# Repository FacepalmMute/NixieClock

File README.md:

# NixieClock
Combining Nixie tube technology with IoT
* Providing vintage style Nixie tube clock suitability for daily use.
* Building of a basis for testing and demonstrating IoT stuff using
  the [ESP8266](
  http://www.google.de/search?hl=de&source=hp&biw=&bih=&q=Mikrocontroller.net+ESP8266
  "Mikrocontroller.net ESP8266 - Google-Suche") in conjunction with
  the Arduino library.
* Open documentation allows designing of individual boxes, using of
  miscellaneous Nixie tubes, software and so forth within your own
  handicraft work.
  
# Firmware
The _firmware_ can be found in the Arduino folder. Compilation was
tested under Arduino.cc. You might use the libraries found in the
library folder. At least you will need the _NixieClock_
software. _DS1307RTC, Time-master_, and _Timezone-master_ are
available in their unimproved versions from Arduino and are assumed to
be yet part of your Arduino standard software installation. When using
the Arduino build system you can use any version you like without
problems.

When using Arduino Eclipse plugins you will get into trouble caused by
the redirection of the standard c-header file _Time.h_ that was done
in _Time-master._ This strange hijacking of the original _time.h_ is
responsible for wrecking the build process of the ESP8266 core
_arduino.ar._ So Eclipse users will likely use my modified versions of
_DS1307RTC, Time-master_, and _Timezone-master_ where I removed the
annoying redirection and detaching of standard headers.

Furthermore there are the two Arduino sketch folders _Nixie4_ and
_Nixie6._ _Nixie4_ is the firmware used by our 4 tube prototype;
_Nixie6_ is used by our 6 tube prototype.

## Prototype with 4 ИН-1 Nixie tubes
![Prototype ИН-1 Nixie clock](./pic/P1010273_s.jpg "4x ИН-1 tube
type")

This clock is an implementation with 4 ИН-1 Nixie tubes. 

## Prototype with 6 ИН-12А Nixie tubes
![Prototype ИН-12А Nixie clock](./pic/P1010278_s.jpg "6x ИН-12А tube
type")

# Hardware Description
![Beware of electric shock!](./pic/High_Voltage.jpg "Beware of
electric shock!")

**Beware of electric shock!**

**Beware of electrical safety hazards!**

**The Nixie tubes are fired at approx 200 Volt! There is definitely a
danger of hazardous voltage given! Never think of working on the Nixie
hardware when you are not educated in doing work with hazardous
voltages!**

The hardware description is given in EAGLE format and a PDF-file.

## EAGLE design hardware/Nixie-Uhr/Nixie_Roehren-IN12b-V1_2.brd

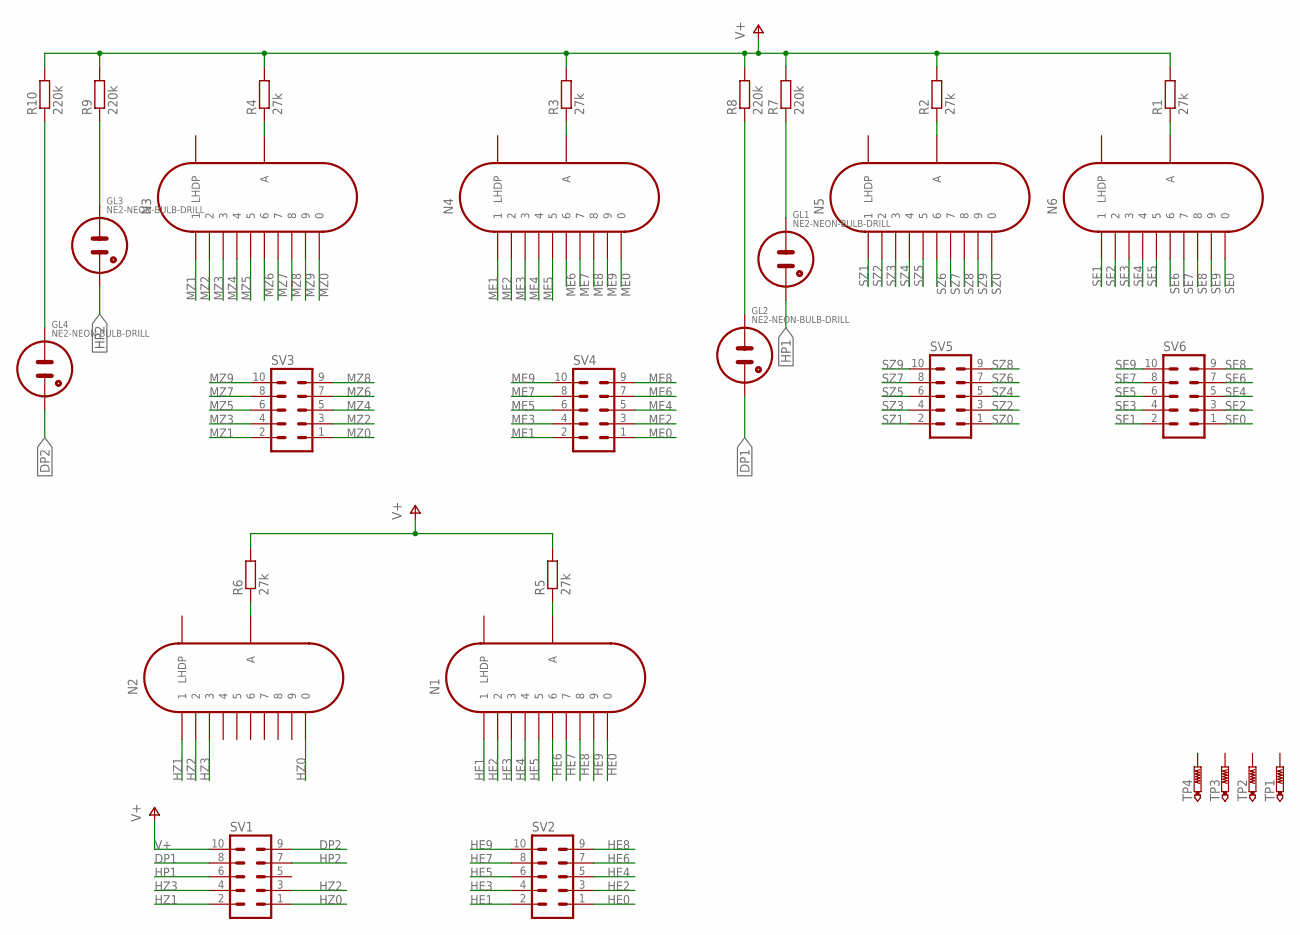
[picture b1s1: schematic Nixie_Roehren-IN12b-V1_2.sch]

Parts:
GL1, GL2, GL3, GL4: NE2-NEON-BULB-DRILL
N1, N2, N3, N4, N5, N6: IN-12B; IN-12
R1, R2, R3, R4, R5, R6: 27k; 0207/10
R7, R8, R9, R10: 220k; 0207/10
SV1, SV2, SV3, SV4, SV5, SV6: ML10
TP1, TP2, TP3, TP4: PTR1B1,27; B1,27

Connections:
DP1: GL2.2 (A1), SV1.8
DP2: GL4.2 (A1), SV1.9
HE0: N1.0, SV2.1
HE1: N1.1, SV2.2
HE2: N1.2, SV2.3
HE3: N1.3, SV2.4
HE4: N1.4, SV2.5
HE5: N1.5, SV2.6
HE6: N1.6, SV2.7
HE7: N1.7, SV2.8
HE8: N1.8, SV2.9
HE9: N1.9, SV2.10
HP1: GL1.2 (A1), SV1.6
HP2: GL3.2 (A1), SV1.7
HZ0: N2.0, SV1.1
HZ1: N2.1, SV1.2
HZ2: N2.2, SV1.3
HZ3: N2.3, SV1.4
ME0: N4.0, SV4.1
ME1: N4.1, SV4.2
ME2: N4.2, SV4.3
ME3: N4.3, SV4.4
ME4: N4.4, SV4.5
ME5: N4.5, SV4.6
ME6: N4.6, SV4.7
ME7: N4.7, SV4.8
ME8: N4.8, SV4.9
ME9: N4.9, SV4.10
MZ0: N3.0, SV3.1
MZ1: N3.1, SV3.2
MZ2: N3.2, SV3.3
MZ3: N3.3, SV3.4
MZ4: N3.4, SV3.5
MZ5: N3.5, SV3.6
MZ6: N3.6, SV3.7
MZ7: N3.7, SV3.8
MZ8: N3.8, SV3.9
MZ9: N3.9, SV3.10
unnamed: N2.A, R6.1
unnamed: N6.A, R1.1
unnamed: N5.A, R2.1
unnamed: N4.A, R3.1
unnamed: N3.A, R4.1
unnamed: GL2.1 (A), R8.1
unnamed: N1.A, R5.1
unnamed: GL1.1 (A), R7.1
unnamed: GL4.1 (A), R10.1
unnamed: GL3.1 (A), R9.1
SE0: N6.0, SV6.1
SE1: N6.1, SV6.2
SE2: N6.2, SV6.3
SE3: N6.3, SV6.4
SE4: N6.4, SV6.5
SE5: N6.5, SV6.6
SE6: N6.6, SV6.7
SE7: N6.7, SV6.8
SE8: N6.8, SV6.9
SE9: N6.9, SV6.10
SZ0: N5.0, SV5.1
SZ1: N5.1, SV5.2
SZ2: N5.2, SV5.3
SZ3: N5.3, SV5.4
SZ4: N5.4, SV5.5
SZ5: N5.5, SV5.6
SZ6: N5.6, SV5.7
SZ7: N5.7, SV5.8
SZ8: N5.8, SV5.9
SZ9: N5.9, SV5.10
V+: R1.2, R2.2, R3.2, R4.2, R5.2, R6.2, R7.2, R8.2, R9.2, R10.2, SV1.10

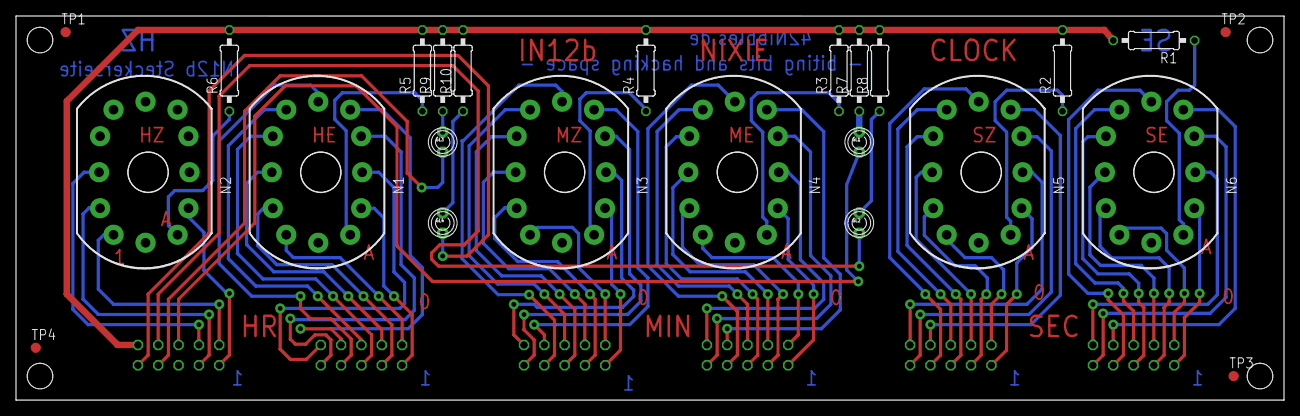
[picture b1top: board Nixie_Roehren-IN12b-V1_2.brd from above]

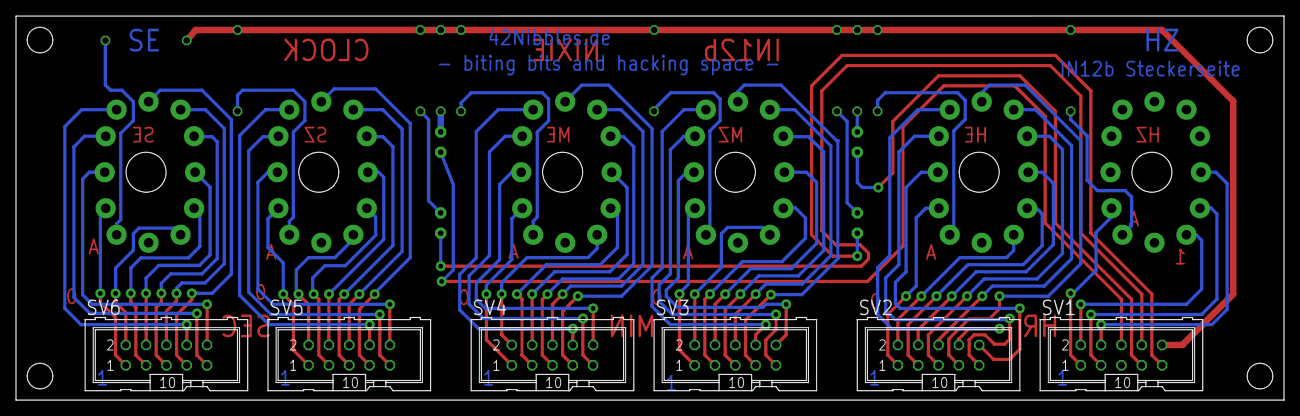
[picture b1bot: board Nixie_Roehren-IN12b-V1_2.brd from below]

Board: 2 copper layers, 158.5 x 48.0 mm, 30 parts (6 on the bottom side), 69 nets.

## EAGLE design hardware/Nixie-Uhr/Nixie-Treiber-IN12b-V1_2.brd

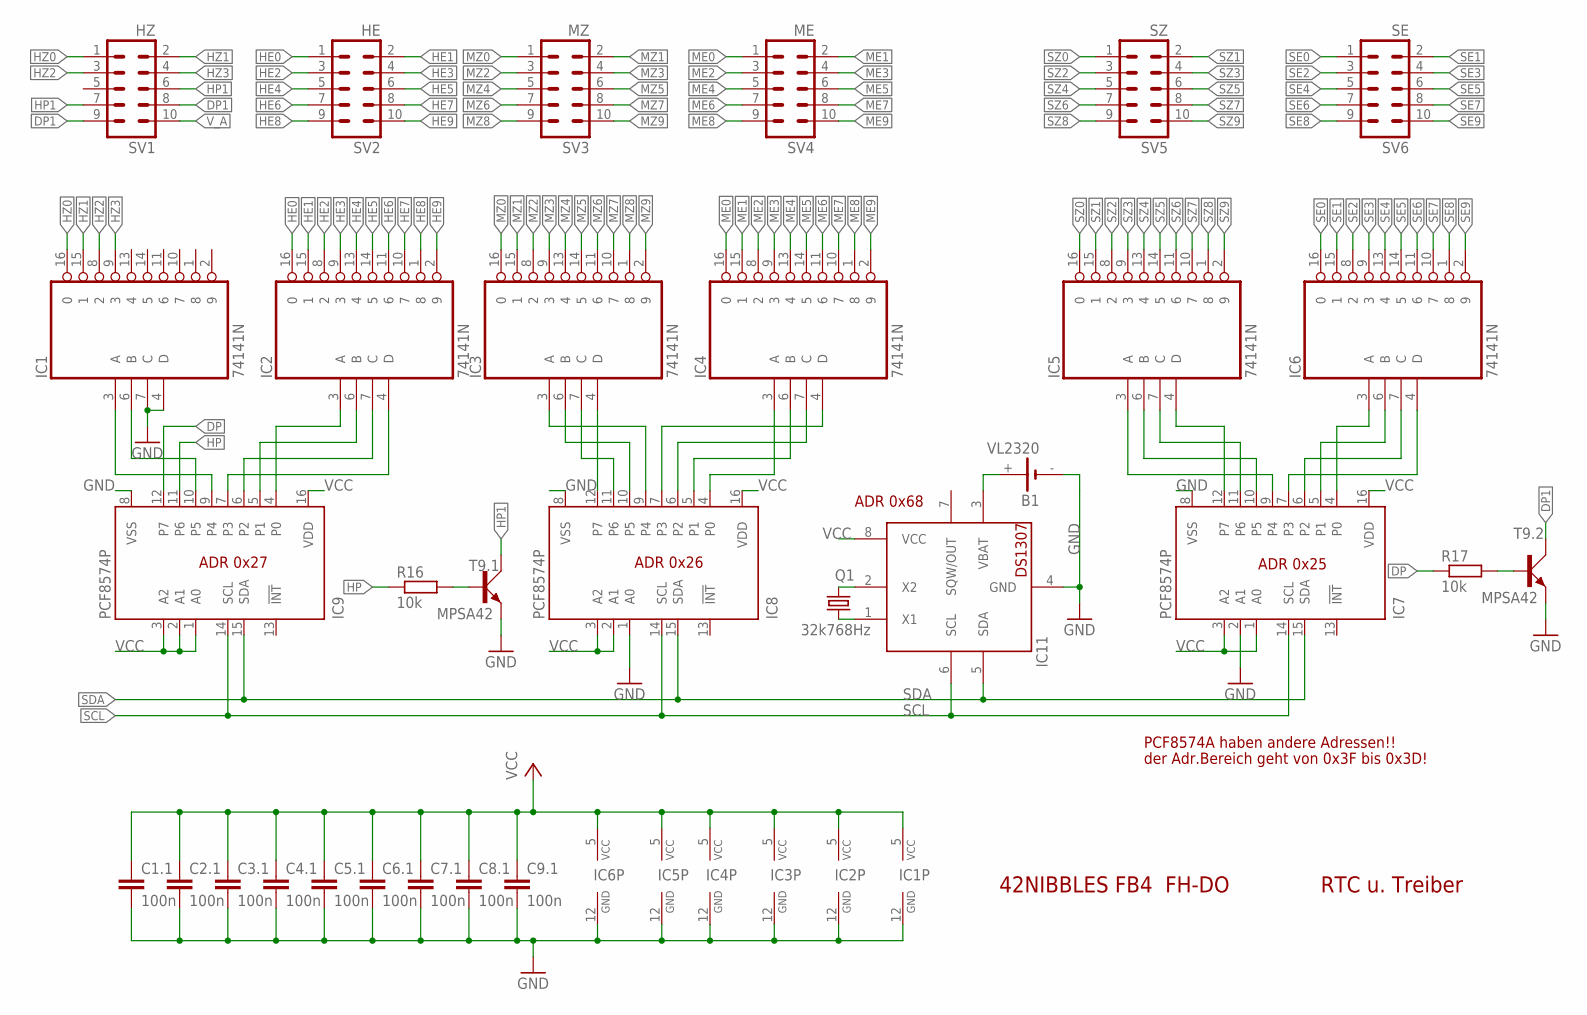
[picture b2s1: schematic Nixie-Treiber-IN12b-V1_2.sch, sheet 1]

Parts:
B1: VL2320
C1.1, C2.1, C3.1, C4.1, C5.1, C6.1, C7.1, C8.1, C9.1: 100n; C050-024X044
IC1, IC2, IC3, IC4, IC5, IC6: 74141N; DIL16
IC7, IC8, IC9: PCF8574P; DIL16
IC11: DS1307; DIL08
Q1: 32k768Hz; TC38H
R16, R17: 10k; 0207/10
SV1: HZ; ML10
SV2: HE; ML10
SV3: MZ; ML10
SV4: ME; ML10
SV5: SZ; ML10
SV6: SE; ML10
T9.1, T9.2: MPSA42; TO92D

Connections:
DP: IC9.12 (P7), R17.1
DP1: SV1.8, SV1.9, T9.2.C
GND: B1.-, C1.1.2, C2.1.2, C3.1.2, C4.1.2, C5.1.2, C6.1.2, C7.1.2, C8.1.2, C9.1.2, IC1.4 (D), IC1.7 (C), IC1.12 (GND), IC2.12 (GND), IC3.12 (GND), IC4.12 (GND), IC5.12 (GND), IC6.12 (GND), IC7.2 (A1), IC7.8 (VSS), IC8.1 (A0), IC8.8 (VSS), IC9.8 (VSS), IC11.4 (GND), T9.1.E, T9.2.E; also elsewhere on the board
HE0: IC2.16 (0), SV2.1
HE1: IC2.15 (1), SV2.2
HE2: IC2.8 (2), SV2.3
HE3: IC2.9 (3), SV2.4
HE4: IC2.13 (4), SV2.5
HE5: IC2.14 (5), SV2.6
HE6: IC2.11 (6), SV2.7
HE7: IC2.10 (7), SV2.8
HE8: IC2.1 (8), SV2.9
HE9: IC2.2 (9), SV2.10
HP: IC9.11 (P6), R16.1
HP1: SV1.6, SV1.7, T9.1.C
HZ0: IC1.16 (0), SV1.1
HZ1: IC1.15 (1), SV1.2
HZ2: IC1.8 (2), SV1.3
HZ3: IC1.9 (3), SV1.4
ME0: IC4.16 (0), SV4.1
ME1: IC4.15 (1), SV4.2
ME2: IC4.8 (2), SV4.3
ME3: IC4.9 (3), SV4.4
ME4: IC4.13 (4), SV4.5
ME5: IC4.14 (5), SV4.6
ME6: IC4.11 (6), SV4.7
ME7: IC4.10 (7), SV4.8
ME8: IC4.1 (8), SV4.9
ME9: IC4.2 (9), SV4.10
MZ0: IC3.16 (0), SV3.1
MZ1: IC3.15 (1), SV3.2
MZ2: IC3.8 (2), SV3.3
MZ3: IC3.9 (3), SV3.4
MZ4: IC3.13 (4), SV3.5
MZ5: IC3.14 (5), SV3.6
MZ6: IC3.11 (6), SV3.7
MZ7: IC3.10 (7), SV3.8
MZ8: IC3.1 (8), SV3.9
MZ9: IC3.2 (9), SV3.10
unnamed: IC2.3 (A), IC9.4 (P0)
unnamed: IC2.6 (B), IC9.5 (P1)
unnamed: IC2.7 (C), IC9.6 (P2)
unnamed: IC2.4 (D), IC9.7 (P3)
unnamed: IC1.3 (A), IC9.9 (P4)
unnamed: IC1.6 (B), IC9.10 (P5)
unnamed: R16.2, T9.1.B
unnamed: R17.2, T9.2.B
unnamed: IC4.3 (A), IC8.4 (P0)
unnamed: IC4.6 (B), IC8.5 (P1)
unnamed: IC4.7 (C), IC8.6 (P2)
unnamed: IC4.4 (D), IC8.7 (P3)
unnamed: IC3.3 (A), IC8.9 (P4)
unnamed: IC3.6 (B), IC8.10 (P5)
unnamed: IC3.7 (C), IC8.11 (P6)
unnamed: IC3.4 (D), IC8.12 (P7)
unnamed: IC6.3 (A), IC7.4 (P0)
unnamed: IC6.6 (B), IC7.5 (P1)
unnamed: IC6.7 (C), IC7.6 (P2)
unnamed: IC6.4 (D), IC7.7 (P3)
unnamed: IC5.3 (A), IC7.9 (P4)
unnamed: IC5.6 (B), IC7.10 (P5)
unnamed: IC5.7 (C), IC7.11 (P6)
unnamed: IC5.4 (D), IC7.12 (P7)
unnamed: IC11.2 (X2), Q1.2
unnamed: IC11.1 (X1), Q1.1
unnamed: B1.+, IC11.3 (VBAT)
SCL: IC7.14 (SCL), IC8.14 (SCL), IC9.14 (SCL), IC11.6 (SCL); also elsewhere on the board
SDA: IC7.15 (SDA), IC8.15 (SDA), IC9.15 (SDA), IC11.5 (SDA); also elsewhere on the board
SE0: IC6.16 (0), SV6.1
SE1: IC6.15 (1), SV6.2
SE2: IC6.8 (2), SV6.3
SE3: IC6.9 (3), SV6.4
SE4: IC6.13 (4), SV6.5
SE5: IC6.14 (5), SV6.6
SE6: IC6.11 (6), SV6.7
SE7: IC6.10 (7), SV6.8
SE8: IC6.1 (8), SV6.9
SE9: IC6.2 (9), SV6.10
SZ0: IC5.16 (0), SV5.1
SZ1: IC5.15 (1), SV5.2
SZ2: IC5.8 (2), SV5.3
SZ3: IC5.9 (3), SV5.4
SZ4: IC5.13 (4), SV5.5
SZ5: IC5.14 (5), SV5.6
SZ6: IC5.11 (6), SV5.7
SZ7: IC5.10 (7), SV5.8
SZ8: IC5.1 (8), SV5.9
SZ9: IC5.2 (9), SV5.10
VCC: C1.1.1, C2.1.1, C3.1.1, C4.1.1, C5.1.1, C6.1.1, C7.1.1, C8.1.1, C9.1.1, IC1.5 (VCC), IC2.5 (VCC), IC3.5 (VCC), IC4.5 (VCC), IC5.5 (VCC), IC6.5 (VCC), IC7.1 (A0), IC7.3 (A2), IC7.16 (VDD), IC8.2 (A1), IC8.3 (A2), IC8.16 (VDD), IC9.1 (A0), IC9.2 (A1), IC9.3 (A2), IC9.16 (VDD), IC11.8 (VCC); also elsewhere on the board
V_A: SV1.10; also elsewhere on the board

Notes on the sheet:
42NIBBLES FB4 FH-DO
RTC u. Treiber
ADR 0x27
ADR 0x26
ADR 0x25
ADR 0x68
PCF8574A haben andere Adressen!!
der Adr.Bereich geht von 0x3F bis 0x3D!

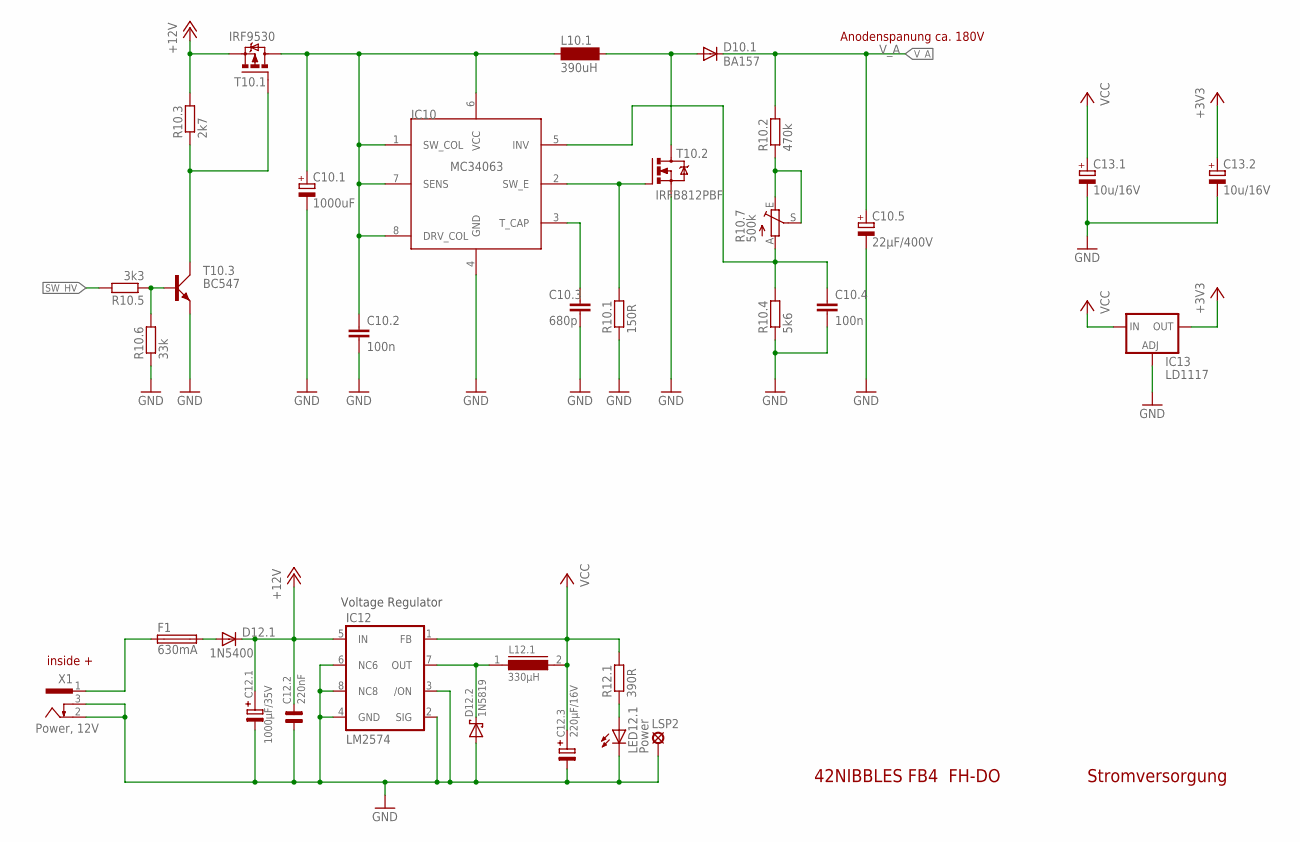
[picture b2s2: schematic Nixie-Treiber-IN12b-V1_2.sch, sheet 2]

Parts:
C10.1: 1000uF; E5-13
C10.2, C10.4: 100n; C050-030X075
C10.3: 680p; C025-025X050
C10.5: 22µF/400V; E5-13
C12.1: 1000µF/35V; E5-13
C12.2: 220nF; C5B2,5
C12.3: 220µF/16V; E5-10,5
C13.1, C13.2: 10u/16V; E1,8-4
D10.1: BA157; DO204-10
D12.1: 1N5400; DO201-15
D12.2: 1N5819; DO35-10
F1: 630mA; SH22,5
IC10: MC34063; DIL08
IC12: LM2574
IC13: LD1117; DPACK
L10.1: 390uH; SD12K100
L12.1: 330µH; SD12-K
LED12.1: Power; LED3MM
LSP2: SE11
R10.1: 150R; 0207/10
R10.2: 470k; 0207/10
R10.3: 2k7; 0207/10
R10.4: 5k6; 0207/10
R10.5: 3k3; 0207/10
R10.6: 33k; 0207/10
R10.7: 500k; ST15
R12.1: 390R; 0207/10
T10.1: IRF9530; TO220BV
T10.2: IRFB812PBF; TO220BV
T10.3: BC547; SOT54A
X1: Power, 12V; HEBW21

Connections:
+3V3: C13.2.+, IC13.4 (OUT); also elsewhere on the board
+12V: C12.1.+, C12.2.2, D12.1.C, IC12.5 (IN), R10.3.2, T10.1.S
GND: C10.1.-, C10.2.2, C10.3.2, C10.4.2, C10.5.-, C12.1.-, C12.2.1, C12.3.-, C13.1.-, C13.2.-, D12.2.A, IC10.4 (GND), IC12.2 (SIG), IC12.3 (/ON), IC12.4 (GND), IC12.6 (NC6), IC12.8 (NC8), IC13.1 (ADJ), LED12.1.K (C), LSP2.MP, R10.1.1, R10.4.1, R10.6.1, T10.2.S, T10.3.E, X1.2, X1.3; also elsewhere on the board
HV_IN: C10.1.+, C10.2.1, IC10.1 (SW_COL), IC10.6 (VCC), IC10.7 (SENS), IC10.8 (DRV_COL), L10.1.1, T10.1.D
unnamed: C10.3.1, IC10.3 (T_CAP)
unnamed: IC10.2 (SW_E), R10.1.2, T10.2.G
unnamed: D10.1.A, L10.1.2, T10.2.D
unnamed: D12.2.K, IC12.7 (OUT), L12.1.1
unnamed: C10.4.1, IC10.5 (INV), R10.4.2, R10.7.A
unnamed: R10.2.1, R10.7.E, R10.7.S
unnamed: LED12.1.A, R12.1.1
unnamed: R10.3.1, T10.1.G, T10.3.C
unnamed: D12.1.A, F1.2
unnamed: R10.5.1, R10.6.2, T10.3.B
SW_HV: R10.5.2; also elsewhere on the board
VCC: C12.3.+, C13.1.+, IC12.1 (FB), IC13.3 (IN), L12.1.2, R12.1.2; also elsewhere on the board
VIN: F1.1, X1.1
V_A: C10.5.+, D10.1.C, R10.2.2; also elsewhere on the board

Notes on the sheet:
Voltage Regulator
42NIBBLES FB4 FH-DO
Stromversorgung
inside +
Anodenspanung ca. 180V

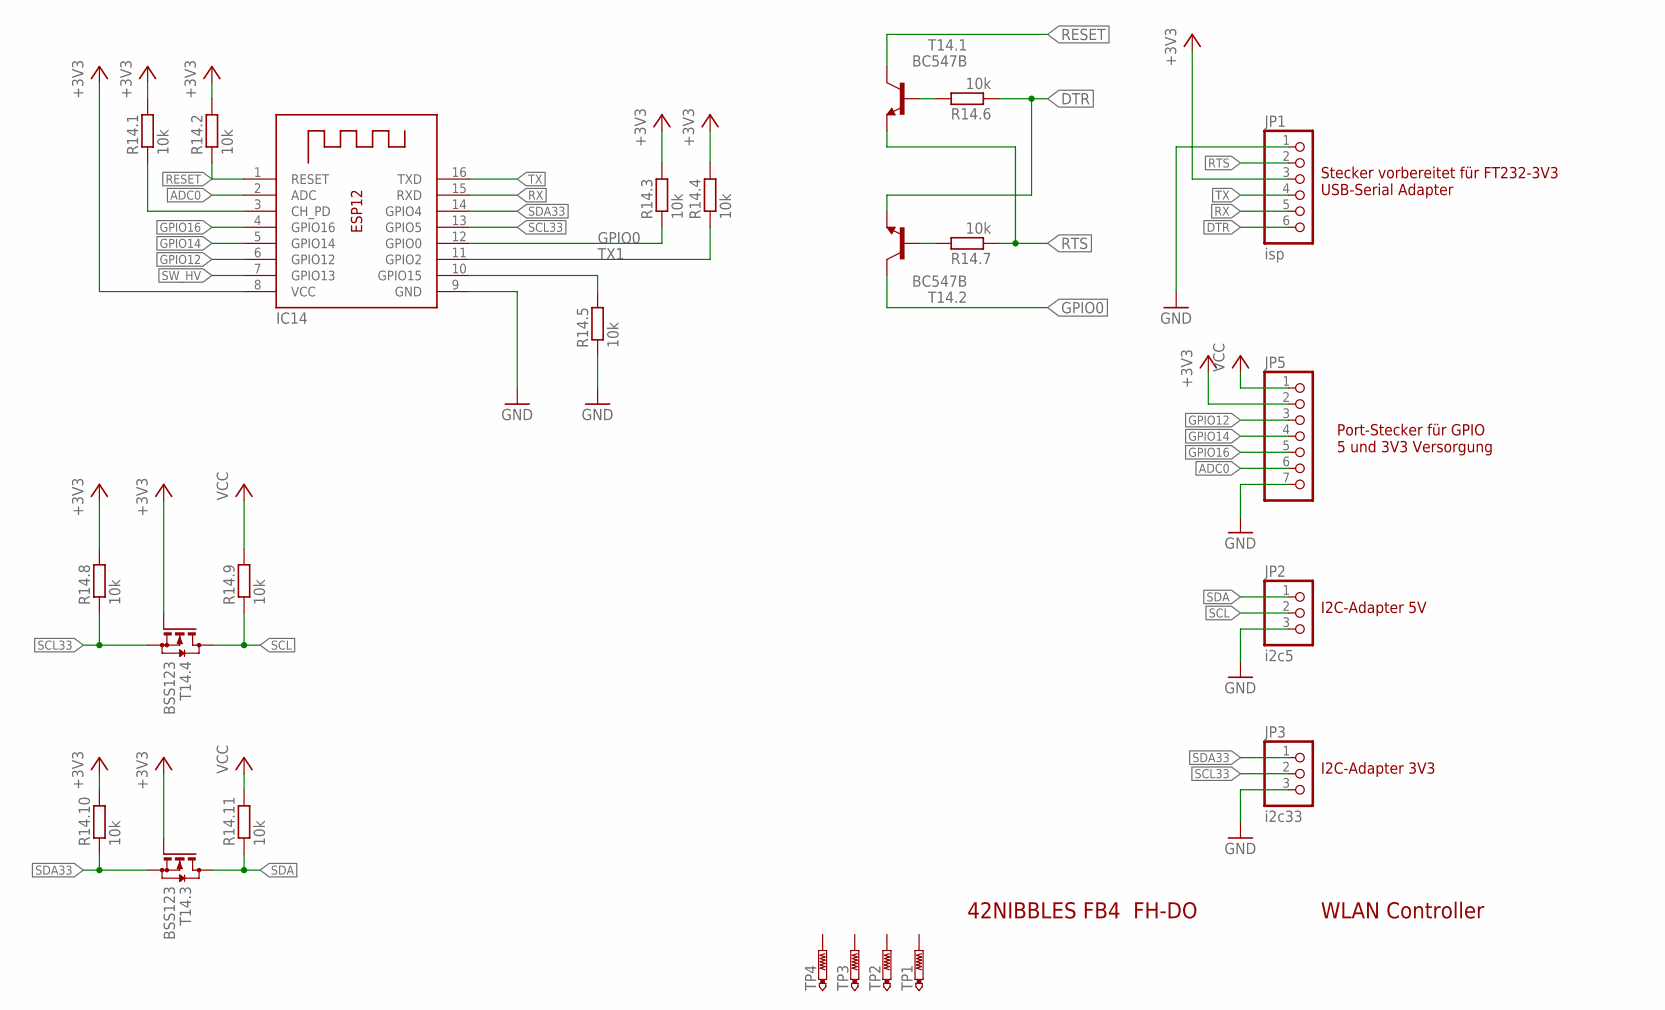
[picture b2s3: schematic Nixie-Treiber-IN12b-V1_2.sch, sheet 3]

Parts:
IC14: ESP07; ESP-12
JP1: isp; 1X06/90
JP2: i2c5; 1X03
JP3: i2c33; 1X03
JP5: PINHD-1X7/90; 1X07/90
R14.1, R14.2, R14.3, R14.4, R14.5, R14.6, R14.7, R14.8, R14.9, R14.10, R14.11: 10k; 0207/10
T14.1, T14.2: BC547B; TO92
T14.3, T14.4: BSS123; SOT23
TP1, TP2, TP3, TP4: PTR1B1,27; B1,27

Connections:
+3V3: IC14.8 (VCC), JP1.3, JP5.2, R14.1.2, R14.2.2, R14.3.2, R14.4.2, R14.8.2, R14.10.2, T14.3.1 (G), T14.4.1 (G); also elsewhere on the board
ADC0: IC14.2 (ADC), JP5.6
DTR: JP1.6, R14.6.1, T14.2.1 (E)
GND: IC14.9 (GND), JP1.1, JP2.3, JP3.3, JP5.7, R14.5.1; also elsewhere on the board
GPIO0: IC14.12 (GPIO0), R14.3.1, T14.2.3 (C)
GPIO12: IC14.6 (GPIO12), JP5.3
GPIO14: IC14.5 (GPIO14), JP5.4
GPIO16: IC14.4 (GPIO16), JP5.5
unnamed: IC14.10 (GPIO15), R14.5.2
unnamed: IC14.3 (CH_PD), R14.1.1
unnamed: R14.7.2, T14.2.2 (B)
unnamed: R14.6.2, T14.1.2 (B)
RESET: IC14.1 (RESET), R14.2.1, T14.1.3 (C)
RTS: JP1.2, R14.7.1, T14.1.1 (E)
RX: IC14.15 (RXD), JP1.5
SCL: JP2.2, R14.9.1, T14.4.3 (D); also elsewhere on the board
SCL33: IC14.13 (GPIO5), JP3.2, R14.8.1, T14.4.2 (S)
SDA: JP2.1, R14.11.1, T14.3.3 (D); also elsewhere on the board
SDA33: IC14.14 (GPIO4), JP3.1, R14.10.1, T14.3.2 (S)
SW_HV: IC14.7 (GPIO13); also elsewhere on the board
TX: IC14.16 (TXD), JP1.4
TX1: IC14.11 (GPIO2), R14.4.1
VCC: JP5.1, R14.9.2, R14.11.2; also elsewhere on the board

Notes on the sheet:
42NIBBLES FB4 FH-DO
WLAN Controller
IC14
Stecker vorbereitet für FT232-3V3 USB-Serial Adapter
I2C-Adapter 5V
I2C-Adapter 3V3
Port-Stecker für GPIO 5 und 3V3 Versorgung

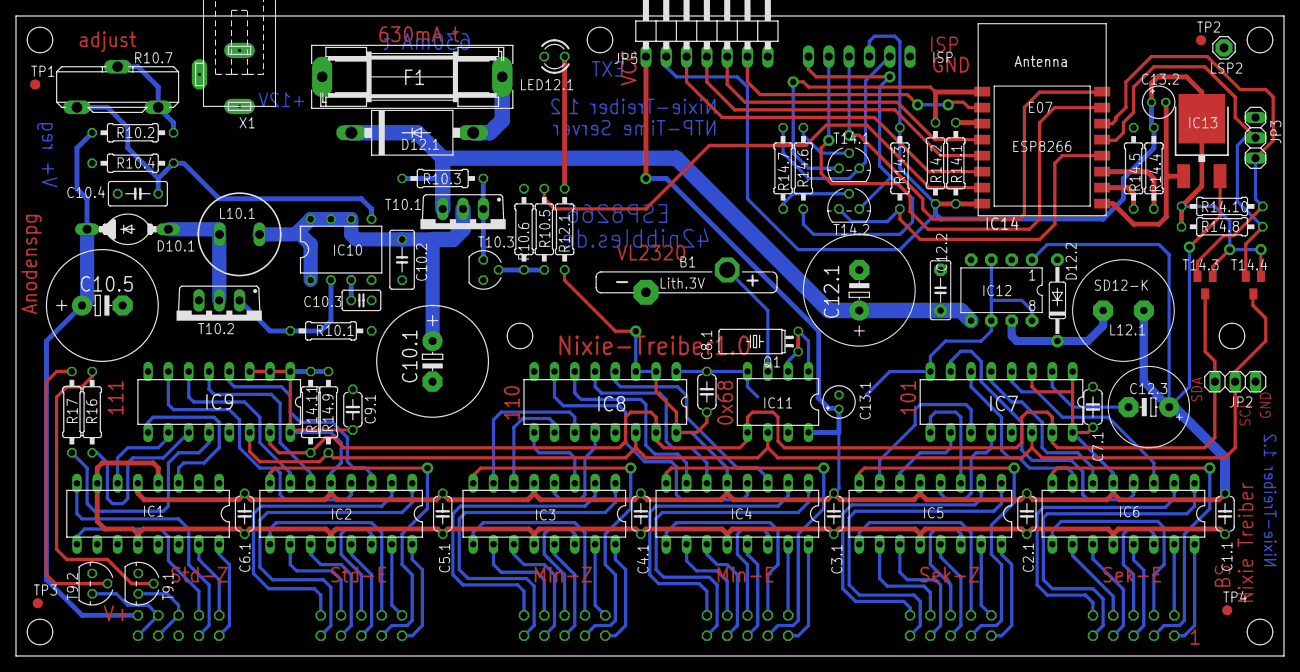
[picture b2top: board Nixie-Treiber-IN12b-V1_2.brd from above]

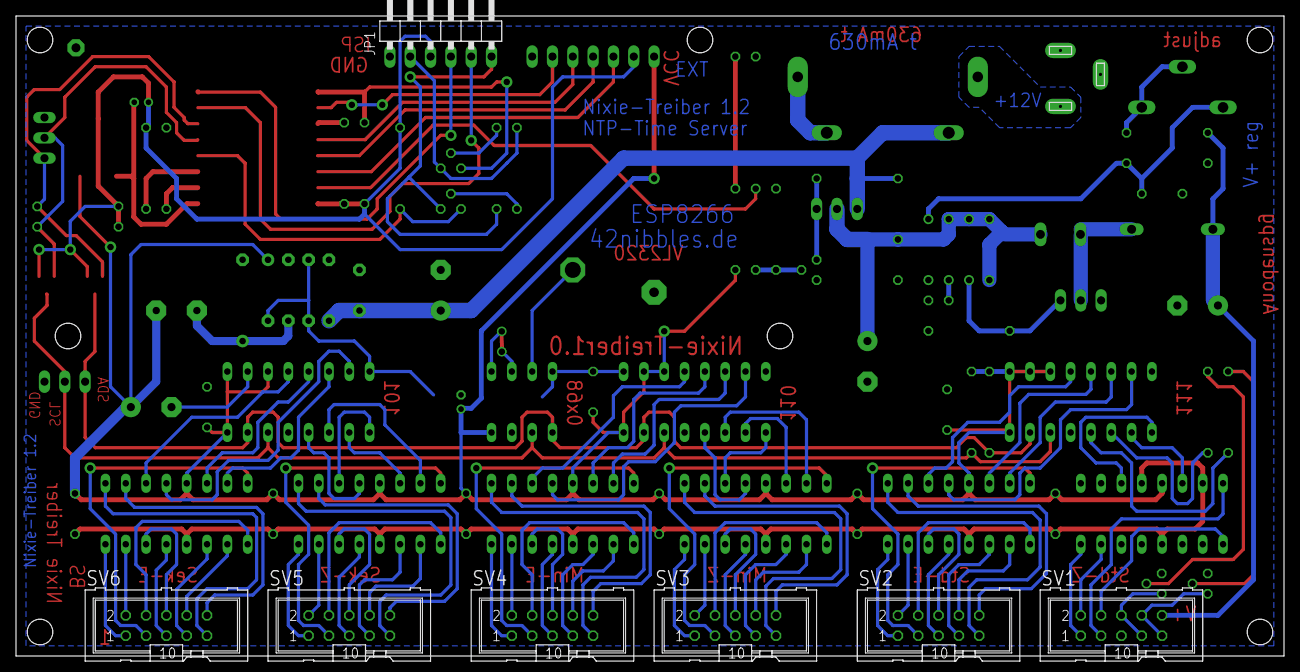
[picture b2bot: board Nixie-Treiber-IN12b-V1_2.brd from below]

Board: 2 copper layers, 158.5 x 80.0 mm, 88 parts (7 on the bottom side), 122 nets.

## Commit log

2017-04-05 Project start.
2017-04-05 Hardware description added.
2017-08-14 Hardware description updated.
2017-09-05 Added WifiManager + OTA support for VFD-IV3A
2017-09-06 Add WifiManager + OTA to current file structure (UNTESTED)
2017-09-30 First Build fixes. (Nixie6)
